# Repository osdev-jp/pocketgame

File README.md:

# PocketGame

[osdev-jp](https://osdev.jp)発のゲーム機開発プロジェクトです。

## ゲーム機の開発コードネーム

### PocketGame Pizza

PocketGame の第 1 世代ゲーム機。
OSC 2026 Tokyo/Fall での展示を目指し、製作を進めています。
リバーシのような盤面を用いた 2 人対戦ゲームがプレイできることが目標です。

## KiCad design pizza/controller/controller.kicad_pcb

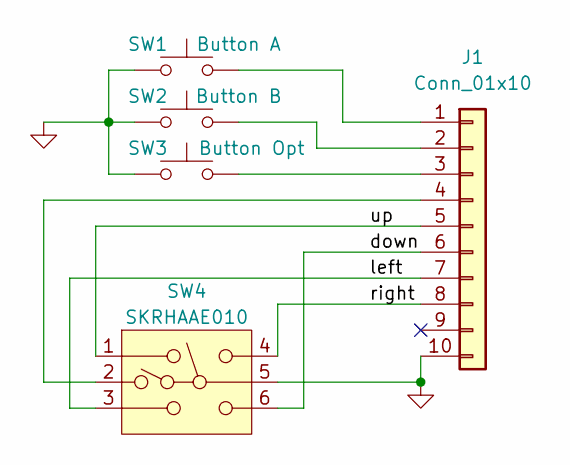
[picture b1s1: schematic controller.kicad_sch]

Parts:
J1: Conn_01x10; PinHeader_1x10_P2.54mm_Horizontal
SW1: Button A; SW_PUSH_6mm
SW2: Button B; SW_PUSH_6mm
SW3: Button Opt; SW_PUSH_6mm
SW4: SKRHAAE010

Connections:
/down: J1.6, SW4.6
/left: J1.7, SW4.3
/right: J1.8, SW4.4
/up: J1.5, SW4.1
GND: J1.10, SW1.1, SW2.1, SW3.1, SW4.5
unnamed: J1.1, SW1.2
unnamed: J1.2, SW2.2
unnamed: J1.3, SW3.2
unnamed: J1.4, SW4.2

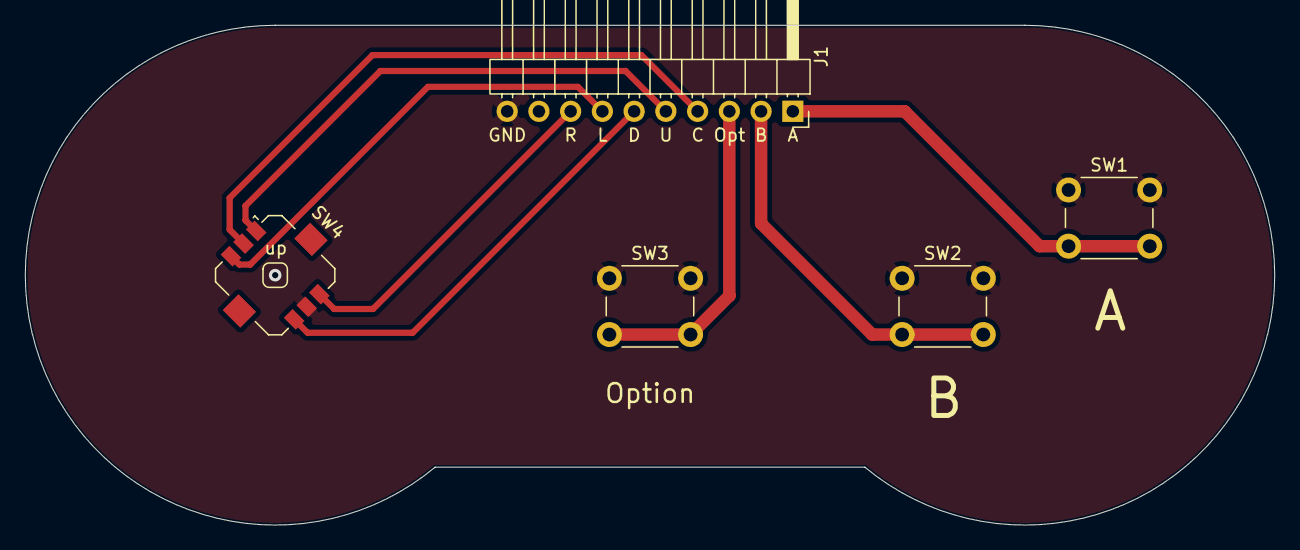
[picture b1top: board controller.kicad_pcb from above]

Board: 2 copper layers, 100.0 x 40.0 mm, 5 parts (0 on the bottom side), 9 nets.

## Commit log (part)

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2026-04-19 真剣白刃取りゲームの試作版を追加
2026-06-14 PocketGame Pizzaのコントローラに使う4方向スイッチのシンボル追加
2026-06-22 コントローラ基板が完成
2026-06-28 開発の役割分担の案を考えた
